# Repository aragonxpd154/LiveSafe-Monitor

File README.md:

# LiveSafe Monitor

Monitoração de sinal de TV e rádio para rodar em Raspberry Pi. Cada Pi fica num abrigo, recebe o sinal do receptor por uma placa de captura HDMI-USB, detecta falhas sozinho e manda trap SNMP. Um servidor LiveSafe central reúne todos os Pis numa tela só e redistribui o vídeo ao vivo de cada local pelo navegador, com um player parecido com o do YouTube.

> **Novo: Placa LiveSafe.** O repositório agora traz também o hardware próprio do LiveSafe — uma placa com
> Raspberry Pi CM4 que recebe **RF ISDB-Tb, HDMI e ASI** direto, sem receptor e sem placa de captura USB, com
> relés e entradas para a remota do abrigo. Esquemático, PCB de 4 camadas e arquivos prontos para a JLCPCB.
> Veja [Placa LiveSafe](#placa-livesafe-hardware).

## O que ele detecta

| Falha | Como | Trap (alarme / normalizado) |
| --- | --- | --- |
| Imagem congelada | menos de 0,1 % dos pixels mudando por 10 s | 2 / 12 |
| Áudio em silêncio | nível abaixo de −60 dBFS por 10 s | 3 / 13 |
| Tela preta | 98 % da tela escura por 5 s | 4 / 14 |
| Sem sinal na entrada | placa ou stream sem entregar dados por 8 s | 5 / 15 |
| Sem comunicação com o Pi (só no central) | Pi não responde por 10 s | 6 / 16 |

Os tempos e limiares são configuráveis por canal. Tela preta tem prioridade sobre congelamento (uma tela preta também está "parada" e não deve gerar dois alarmes). Durante uma queda de sinal os outros detectores ficam suspensos, então não chegam traps falsas de congelamento ou silêncio.

## Como funciona

```
 Abrigo (um Pi em cada)                         Sala de controle

 Receptor ──HDMI──▶ placa HDMI-USB ──USB──┐
                                          ▼
 ┌─────────────────────────────────────────┐   HTTP/TCP    ┌──────────────────────────────┐
 │ Raspberry Pi 4 - LiveSafe de borda      │──────────────▶│ Servidor LiveSafe central    │
 │  • detecta falhas e manda traps         │ estado (SSE)  │  • estado de todos os Pis    │
 │  • gera o stream HLS na RAM             │ vídeo (HLS)   │  • alarme "sem comunicação"  │──▶ navegadores
 └─────────────────────────────────────────┘               │  • repassa o vídeo com cache │    (painel e player)
                                                           └──────────────────────────────┘
```

- **Um ffmpeg por canal.** Decodifica uma única vez e entrega: quadros 160×90 em cinza para a análise, áudio de 16 kHz para os medidores, um JPEG por segundo para a miniatura e o stream ao vivo em HLS (H.264 + AAC).
- **Sem UDP no enlace.** Tudo entre o Pi e o central é HTTP sobre TCP: o estado vai por uma única conexão Server-Sent Events e o vídeo em segmentos HLS de 1 s. Nada de multicast ou fluxo UDP contínuo saindo do abrigo.
- **O enlace só carrega o que está sendo assistido.** O central busca cada segmento do Pi uma vez e entrega para todos que estão assistindo. Dez pessoas olhando Pedra Azul geram um único download até Pedra Azul.
- **Buffer pequeno.** Segmentos de 1 s e player sincronizado a 3 segmentos do ao vivo: atraso típico de 3 a 4 s. A barra do player permite voltar até 30 s.
- **Feito para o Pi.** Codificação H.264 por hardware (`h264_v4l2m2m`) no Pi 4, com troca automática para software se o hardware não estiver disponível. O HLS fica em `/run/livesafe` (RAM) e o log vai para o journald, então o cartão SD quase não é escrito.
- **Se recupera sozinho**, em camadas (detalhes abaixo).
- **Leve.** Só duas dependências npm (`net-snmp` e o `hls.js` do player), servidor HTTP nativo do Node, painel sem CDN que funciona numa rede sem internet.

## Recuperação automática

Um Pi num abrigo não tem ninguém do lado para apertar botão, então cada tipo de falha tem quem cuide dela:

| O que acontece | Quem resolve | Tempo até voltar |
| --- | --- | --- |
| Pi reinicia (falta de energia, reboot) | systemd sobe o LiveSafe no boot; se a placa HDMI-USB demorar a aparecer, a captura tenta de novo sozinha | o tempo do boot + até 30 s |
| ffmpeg cai | LiveSafe religa com espera crescente (2, 4, 8… até 30 s) | 2 s na primeira vez |
| ffmpeg trava sem cair (comum com placa USB) | vigia interno: 8 s sem quadros ou áudio, mata e religa | ~10 s |
| Entrada normal, mas o stream ao vivo parou | vigia interno: playlist parada por 10 s, reinicia a captura e registra a ocorrência | ~15 s |
| LiveSafe cai | systemd religa em 3 s e derruba junto qualquer ffmpeg órfão | 3 s |
| LiveSafe trava sem cair | `livesafe-watchdog.timer`: a cada 30 s testa o `/healthz`; 3 falhas seguidas, reinicia o serviço | até ~1 min |
| Memória dispara | teto de 1,2 GB no systemd; o serviço é reiniciado | 3 s |
| Pi inteiro congela (kernel, calor) | watchdog de hardware do Raspberry Pi: reinicia a placa | 14 s + boot |
| Enlace com o abrigo cai | central alarma "sem comunicação", reconecta sozinho e traz as ocorrências do período fora; o player tenta de novo a cada 3 s | assim que o enlace volta |

Num Raspberry Pi, o instalador pergunta se deve ligar o watchdog de hardware (recomendado; pode pedir um reboot na primeira vez). O que o vigia fez fica em `journalctl -t livesafe-watchdog`.

## Player ao vivo

Clique em **Assistir ao vivo** em qualquer canal. A barra mostra o que já foi carregado (cinza claro) e onde você está (vermelho); o selo **Ao vivo** fica vermelho quando você está na ponta e, se você voltar no tempo, um clique nele traz de volta. **Estatísticas** mostra resolução, taxa, banda medida, buffer à frente, atraso em relação ao ao vivo e quadros perdidos. Atalhos: espaço pausa, `M` silencia, `F` tela cheia, setas voltam ou avançam 5 s.

Canais só de áudio (rádios FM) ganham medidores grandes no lugar da imagem e o botão **Ouvir ao vivo**.

| Pi de borda | Celular |
| :---: | :---: |
|  |  |

## Instalação

Requisitos: Raspberry Pi 4 (2 GB ou mais) com Raspberry Pi OS Bookworm 64 bits, de preferência a versão Lite. O servidor central pode ser outro Pi ou qualquer Debian/Ubuntu.

A instalação tem duas partes: o **instalador** pergunta pelo terminal (SSH) o papel da máquina, o nome do local e a senha do painel, e instala tudo; depois, o **assistente no navegador** configura a placa de captura (Pi) ou os Pis dos abrigos (central).

### 1. Instalar

Escolha um dos três caminhos. Os três usam o mesmo instalador e servem tanto para o Pi de borda quanto para o central.

**Com internet (GitHub):**

```bash
curl -fsSL https://raw.githubusercontent.com/aragonxpd154/LiveSafe-Monitor/main/install.sh | sudo bash
```

**Pelo servidor central**, para Pis que enxergam o central mas não a internet. O assistente do central mostra este comando já com o IP certo:

```bash
curl -fsSL http://<ip-do-central>:8080/instalar.sh | sudo bash
```

**Sem internet (pendrive).** Baixe `livesafe-offline-arm64.tar.gz` na página de [releases](https://github.com/aragonxpd154/LiveSafe-Monitor/releases/latest). O arquivo tem cerca de 250 MB e já traz o ffmpeg, o Node.js e todas as dependências para o Raspberry Pi OS Bookworm 64 bits. No Pi:

```bash
tar -xzf livesafe-offline-arm64.tar.gz
sudo ./livesafe-monitor/install.sh
```

Se o central for instalado a partir do pacote offline, ele guarda esses pacotes e os entrega aos Pis que instalarem pelo segundo caminho. Assim, um Pi sem internet instala tudo só falando com o central.

**Gerar o pacote offline no seu PC.** Não precisa de Pi nem de sudo: qualquer computador Debian/Ubuntu com internet (Zorin OS, por exemplo) monta o pacote para o Raspberry Pi OS Bookworm 64 bits, sem instalar nada no PC:

```bash
sudo apt install dpkg-dev debian-archive-keyring gnupg curl   # só na primeira vez
./scripts/build-offline-bundle.sh --pi                         # gera dist/livesafe-offline-arm64.tar.gz
```

O script baixa os pacotes dos repositórios oficiais do Debian e do Raspberry Pi, conferindo as assinaturas, e leva poucos minutos. Rodando com `sudo` e sem `--pi` num Pi com internet, ele gera o pacote para o sistema daquele Pi. O GitHub Actions também gera os dois pacotes a cada tag `v*` (workflow `release.yml`).

Rodar o instalador de novo atualiza o LiveSafe e mantém a configuração, os canais e as senhas.

<details>
<summary>Instalação automatizada, sem perguntas</summary>

```bash
curl -fsSL …/install.sh | sudo LIVESAFE_NONINTERACTIVE=1 LIVESAFE_ROLE=edge LIVESAFE_SITE="Pedra Azul" LIVESAFE_PASSWORD='…' bash
```

`LIVESAFE_ROLE` é `edge` ou `central`. Sem `LIVESAFE_PASSWORD`, uma senha é gerada e mostrada no fim. `LIVESAFE_HW_WATCHDOG=0` não liga o watchdog de hardware.
</details>

### 2. Configurar no navegador

Ao terminar, o instalador mostra o endereço `http://<ip>:8080/setup`. Entre com o usuário `admin` e a senha que você criou.

- **No Pi de borda**, o assistente procura a placa HDMI-USB, sugere o formato e a resolução, e o botão **Testar entrada** mostra um quadro do receptor e o nível do áudio antes de salvar. Também dá para usar um endereço de rede (UDP do IRD, RTSP, HTTP) ou montar um canal só de rádio.
- **No central**, você cadastra cada Pi pelo IP e pela senha dele; **Testar conexão** confirma o nome do abrigo e os canais.
- As etapas seguintes definem os destinos das traps, os tempos de alarme e a qualidade do vídeo ao vivo. Ao salvar, o LiveSafe reinicia já com a configuração nova.

| Pi de borda: entrada de sinal | Central: Pis dos abrigos |
| :---: | :---: |
|  |  |

O assistente continua disponível em `/setup` para mudanças futuras. Logs ao vivo: `journalctl -u livesafe -f`.

## Configuração manual

O assistente grava `/var/lib/livesafe/config.json`, que também pode ser editado à mão (depois, `sudo systemctl restart livesafe`). Há dois exemplos: [`config.edge.example.json`](config.edge.example.json) (Pi de borda) e [`config.central.example.json`](config.central.example.json) (servidor central). A senha do painel é guardada como hash (`passwordHash`); `password` em texto também é aceito.

### Canal com placa HDMI-USB

As placas baratas com chip MS2109 entregam MJPEG e aparecem como duas entradas: vídeo em `/dev/video0` e áudio no ALSA.

```json
{
  "id": "hdmi",
  "name": "Receptor TV Gazeta (HDMI)",
  "inputArgs": [
    "-f", "v4l2", "-input_format", "mjpeg", "-video_size", "1280x720", "-framerate", "30", "-i", "/dev/video0",
    "-f", "alsa", "-channels", "2", "-sample_rate", "48000", "-i", "hw:CARD=MS2109,DEV=0"
  ],
  "videoStream": "0:v:0",
  "audioStream": "1:a:0"
}
```

Outras entradas que o ffmpeg abre também servem, com `"url"` no lugar de `inputArgs`: `udp://@239.10.10.1:1234` (IRD), `rtsp://…`, `http://…`. Para escolher um serviço dentro de um transport stream com vários programas, use por exemplo `"videoStream": "0:p:57345:v:0"`. Rádio só com áudio: `"video": false`.

### Servidor central

```json
"sites": [
  { "id": "pedra-azul", "name": "Pedra Azul", "url": "http://10.10.8.21:8080", "user": "livesafe", "password": "…" }
]
```

`user` e `password` são o usuário e a senha do painel daquele Pi.

### Ajustes mais usados

| Chave | Padrão | Para que serve |
| --- | --- | --- |
| `freeze.seconds`, `freeze.motionPct` | 10 s, 0,1 % | Tolerância a cenas paradas (cartelas, vinhetas). Veja o "Movimento" no painel para calibrar. |
| `black.seconds`, `black.pct` | 5 s, 98 % | Tela preta. |
| `silence.seconds`, `silence.dbfs` | 10 s, −60 dBFS | Silêncio. Rádio costuma precisar de mais tempo. |
| `signal.stallSeconds` | 8 s | Tempo sem dados até "sem sinal". |
| `stream.bitrate`, `stream.width`, `stream.fps` | 2000k, 1280, 25 | Qualidade do vídeo ao vivo. Reduza se o enlace do abrigo for estreito. |
| `stream.windowSeconds` | 30 | Quanto dá para voltar na barra do player. |
| `stream.encoder` | `auto` | `auto`, `h264_v4l2m2m` (hardware do Pi 4) ou `libx264`. |
| `stream.softwareMaxWidth` | 854 | Largura máxima quando a codificação cai para software, para não saturar a CPU. |
| `central.offlineSeconds` | 10 | Tempo sem resposta até "sem comunicação com o Pi". |
| `snmp.traps.version` | `"1"` | `"1"` (como nas versões anteriores) ou `"2c"`. |
| `snmp.agent.enabled` | `false` | Liga o agente SNMP para o NMS consultar o estado (GET/WALK). |

## SNMP

Toda trap leva os mesmos varbinds, sob o enterprise `1.3.6.1.4.1.53864` usado desde a primeira versão:

| OID | Tipo | Conteúdo |
| --- | --- | --- |
| `.1.1` | Integer | código da tabela acima (1 = LiveSafe iniciado, 9 = trap de teste) |
| `.1.2` | Integer | número do canal |
| `.1.3` | OctetString | nome do canal |
| `.1.4` | OctetString | mensagem em português |
| `.1.5` | OctetString | id do canal |

Em SNMPv1 a trap vai como enterprise `1.3.6.1.4.1.53864.0`, specific = código; em v2c o `snmpTrapOID` é `1.3.6.1.4.1.53864.0.<código>`. O botão **Enviar trap de teste** no painel serve para conferir a chegada no NMS.

Com o agente ligado, a tabela `1.3.6.1.4.1.53864.2.1.1.<coluna>.<canal>` traz índice, id, nome, estado geral (1 normal, 2 observação, 3 alarme, 4 iniciando), estado de sinal, congelamento, tela preta e silêncio (0 desligado, 1 normal, 2 suspeita, 3 alarme), movimento ×100, nível de áudio em dBFS ×10 e reinícios. `1.3.6.1.4.1.53864.3.2.0` é o total de alarmes ativos.

```bash
snmpwalk -v2c -c public <ip-do-pi>:1161 1.3.6.1.4.1.53864
```

## API

| Método e rota | O que faz |
| --- | --- |
| `GET /api/state` | Estado completo (canais, Pis, saúde, últimas ocorrências) |
| `GET /api/stream` | Estado ao vivo por Server-Sent Events |
| `GET /api/events?limit=100` | Histórico de ocorrências |
| `GET /hls/<canal>/index.m3u8` | Stream ao vivo do canal (abre também no VLC) |
| `GET /api/channels/<canal>/snapshot.jpg` | Última miniatura |
| `GET /api/channels/<canal>/live.mjpg` | MJPEG contínuo, para multiviewers |
| `POST /api/channels/<canal>/restart` | Reinicia a captura |
| `POST /api/test-trap` | Envia trap de teste |
| `GET /healthz` | Saúde do serviço, sem autenticação; responde 503 se o laço interno parou (usado pelo vigia) |
| `/sites/<pi>/…` | No central: as mesmas rotas de um Pi, repassadas com cache |

## Testar sem placa de captura

```bash
./scripts/test-signal.sh udp://127.0.0.1:5000
```

Gera um sinal em loop com trechos de imagem normal, congelada, preta e silêncio. Aponte um canal para `udp://127.0.0.1:5000` e acompanhe os alarmes. Parar o script testa o "sem sinal". Testes automáticos: `npm test`.

## Placa LiveSafe (hardware)

Hoje o LiveSafe roda num Raspberry Pi 4 com uma placa de captura HDMI-USB ligada ao receptor. A Placa LiveSafe
junta tudo numa placa só, instalada em cada abrigo, e acrescenta as entradas que faltavam:

| Entrada | Caminho | O que o LiveSafe ganha |
|---|---|---|
| **RF ISDB-Tb (UHF)** | BNC 75 Ω → Si2141 → Si2183-B60 → FX2LP → USB | o sinal do ar, sem IRD; C/N e BER do canal |
| **HDMI** | HDMI → TC358743XBG → CSI-2 (4 vias) + I2S | a saída do IRD/receptor sem placa de captura |
| **ASI** | BNC 75 Ω → GS2961A → FX2LP → USB | o transport stream do encoder ou do multiplexador |

Saídas: Ethernet Gigabit (painel web, HLS, SNMP), 4 relés SPDT e 4 entradas optoacopladas para a remota do
abrigo, RTC com bateria, controle de ventoinha. Alimentação única de **12 V** (9 a 18 V). O software é este
mesmo LiveSafe Monitor; o que muda no lado do software está em [docs/06](docs/06-software-e-drivers.md).

### Situação

| Etapa | Situação |
|---|---|
| Escolha dos chips e arquitetura | ✅ [docs/01](docs/01-arquitetura.md) |
| Pinagens conferidas nos datasheets (Si2183, Si2141, GS2961A) | ✅ `tools/pinagens.py` |
| Esquemático (9 folhas, netlist conferida pelo KiCad) | ✅ [PDF](hardware/esquema-eletrico-completo.pdf) · [docs/02](docs/02-esquematico.md) |
| PCB 4 camadas 160 × 100 mm — **DRC limpo (0 erros, 0 ligações pendentes)** | ✅ [docs/03](docs/03-pcb.md) |
| Arquivos JLCPCB (Gerber, BOM com código LCSC, CPL, STEP) | ✅ [docs/04](docs/04-fabricacao-jlcpcb.md) |
| Protótipo de bancada com módulos prontos | ⏳ [docs/07](docs/07-prototipo-de-bancada.md) |
| Primeira placa fabricada e testada | ⏳ [docs/05](docs/05-montagem-e-testes.md) |

> **Revisão antes de fabricar.** É a revisão 1.0, nunca fabricada. Os pontos em aberto estão em
> [docs/08](docs/08-revisao-e-riscos.md): rede de entrada de RF do Si2141 (datasheet completo sob NDA), pares
> diferenciais roteados automaticamente, disponibilidade do TC358743 e as rotações da montagem JLCPCB.
> Recomenda-se a revisão de um projetista de hardware e um lote pequeno (5 placas) antes da produção.

| Topo | Fundo |
| :---: | :---: |
|  |  |

O [visualizador 3D](docs/3d/visualizador.html) abre o modelo com as camadas reais de cobre, máscara e serigrafia
(com o GitHub Pages ligado no repositório, ele abre direto em
`https://aragonxpd154.github.io/LiveSafe-Monitor/docs/3d/visualizador.html`). O modelo mecânico está em
`hardware/fabricacao/livesafe-placa/livesafe-placa.step`.

### Fabricar

1. Gerber: `hardware/fabricacao/livesafe-placa/livesafe-placa-gerber.zip` — 4 camadas, 1,6 mm, impedância
   controlada **JLC04161H-7628**, ENIG.
2. Montagem: `bom-jlcpcb.csv` + `cpl-jlcpcb.csv` (face de cima), com código LCSC em todas as linhas. Conferir
   as rotações na pré-visualização.
3. `pecas-fora-da-jlcpcb.csv`: conectores de furo (solda manual), TC358743 e indutor de 6,8 µH (*Global
   Sourcing*), CM4 (CM4104032) e bateria CR1220, que entram depois, à mão.

Passo a passo completo em [docs/04](docs/04-fabricacao-jlcpcb.md); primeiros testes em [docs/05](docs/05-montagem-e-testes.md).

### Arquivos da placa

| Pasta | O que tem |
|---|---|
| `hardware/kicad/livesafe-placa/` | projeto KiCad 7 (esquemático hierárquico e PCB) |
| `hardware/kicad/bibliotecas/` | símbolos e footprints próprios (CM4, TC358743 BGA-64 0,65 mm, Si2141 com pads de canto) |
| `hardware/fabricacao/livesafe-placa/` | Gerber, BOM, CPL, STEP, PDFs de conferência, relatório de DRC |
| `hardware/esquema-eletrico-completo.pdf` | o esquema completo |
| `docs/` | arquitetura, esquemático, PCB, fabricação, testes, software, protótipo de bancada, riscos; imagens e 3D |
| `tools/gerador-kicad/` | o gerador: `designs.py` (todas as ligações), `layouts.py` (planta), `pcbgen.py`, `completar.py` (roteador de acabamento), `lcsc.py` (códigos LCSC), `fabricacao.py` |
| `ref/` | pinagens conferidas (JSON) e referências de terceiros |

<details>
<summary>Gerar a placa de novo a partir do código</summary>

```bash
sudo apt install kicad openjdk-21-jre xvfb python3-pip  # KiCad 7 ou mais novo
pip install trimesh cascadio playwright pillow numpy pypdf
cd tools/gerador-kicad
wget https://github.com/freerouting/freerouting/releases/download/v1.9.0/freerouting-1.9.0.jar
/usr/bin/python3 gerar_tudo.py              # esquemático, PCB roteada (Freerouting + completar.py), DRC e JLCPCB
python3 ../diagramas.py                     # diagrama de blocos
python3 ../render3d.py && python3 ../render_imagens3d.py   # modelo 3D e imagens
```

O Freerouting não é determinístico: cada rodada sai diferente e pode precisar de acabamento
([docs/03](docs/03-pcb.md)). A placa versionada é a referência. Para só atualizar valores e códigos das peças
sem mexer no cobre: `sincronizar.py`. Regerar **substitui** os arquivos do KiCad.
</details>

## Estrutura

```
install.sh      instalador com telas no terminal (online, pelo central ou offline)
src/
  index.js      inicialização, laço de 1 s, /healthz e encerramento limpo
  channel.js    um canal: processo ffmpeg, análise, religamento, HLS
  detectors.js  análise de quadro, níveis de áudio e histerese
  encoder.js    escolha do encoder H.264 (hardware do Pi ou software)
  remote.js     servidor central: conexão com os Pis e cache do proxy
  setup.js      assistente: testar entrada, testar Pi, salvar e reiniciar
  devices.js    descoberta de placas V4L2 e ALSA
  installer.js  /instalar.sh e o pacote servidos pelo central
  auth.js       senha do painel (hash scrypt, bloqueio após erros)
  snmp.js       traps e agente SNMP
  web.js        servidor HTTP, SSE, HLS e proxy
  events.js     histórico de ocorrências
  system.js     temperatura, CPU e memória do host
public/         painel, player e assistente (sem dependências externas)
deploy/         instalação sem perguntas, serviço systemd e vigia (watchdog)
scripts/        descoberta de placas, sinal de teste e geração dos pacotes
legacy/         versões 1 a 4, só para consulta

hardware/       Placa LiveSafe: projeto KiCad, esquema em PDF e arquivos de fabricação (JLCPCB)
docs/           documentação da placa (01 a 08), imagens e visualizador 3D
tools/          gerador da placa por código (KiCad + Freerouting) e scripts das imagens
ref/            pinagens conferidas nos datasheets e referências de terceiros
```

## Histórico

A versão 5 reescreve o projeto. As versões anteriores dependiam de uma aba do navegador aberta (v1/v2) ou do Windows com DirectShow (v3), e o painel vinha de outro projeto, com bibliotecas carregadas de CDNs que já saíram do ar. O código antigo está em [`legacy/`](legacy/), sem os executáveis do ffmpeg para Windows que ocupavam cerca de 500 MB do repositório.

Em novembro de 2026 entrou a **Placa LiveSafe** (revisão 1.0 do hardware), descrita acima e no
[CHANGELOG](CHANGELOG.md).

## Autor

**Marcos Silva dos Santos** (MarcosObel) — [github.com/aragonxpd154](https://github.com/aragonxpd154)

## Licença

- **Software** (`src/`, `public/`, `deploy/`, `scripts/`, `install.sh` e o resto do LiveSafe Monitor): **MIT**.
  Veja [LICENSE](LICENSE).
- **Placa LiveSafe** (`hardware/`, `docs/`, `tools/`, `ref/`): **CERN-OHL-S-2.0**. Veja
  [hardware/LICENSE](hardware/LICENSE). Partes de terceiros mantêm a licença original: circuito de referência
  do TC358743 e footprint do DF40 (Antmicro, Apache-2.0), footprint do CM4 (Raspberry Pi Ltd., projeto KiCad da
  placa CM4IO, CC BY 4.0), SDK do Si2183/Si2141 (Skyworks, Apache-2.0).

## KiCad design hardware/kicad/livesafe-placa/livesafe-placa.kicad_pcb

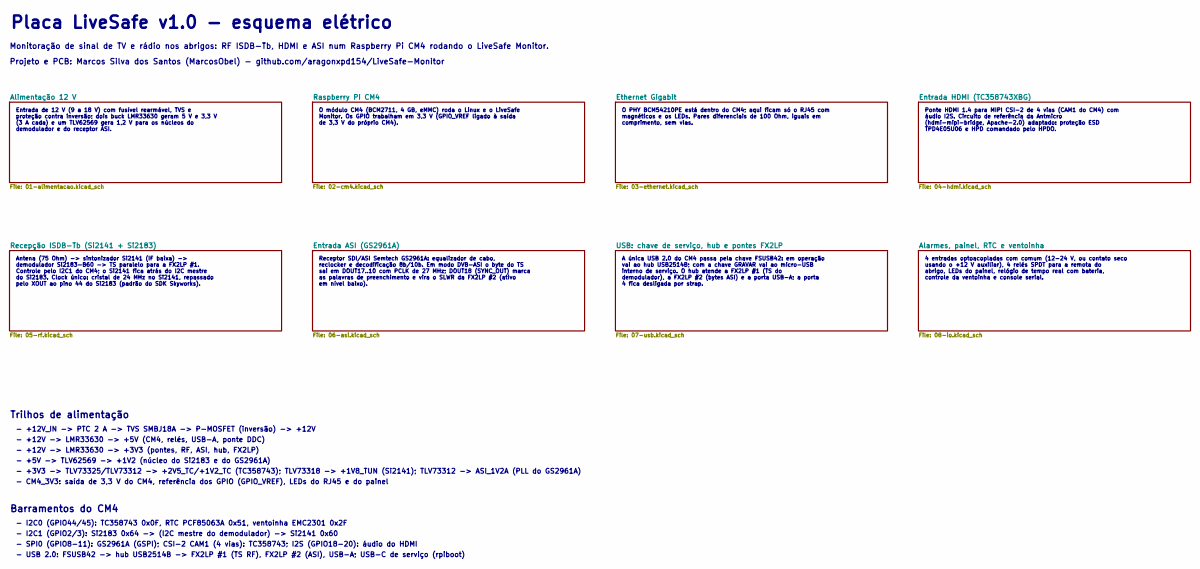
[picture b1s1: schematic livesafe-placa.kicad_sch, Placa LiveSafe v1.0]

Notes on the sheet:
Placa LiveSafe v1.0 - esquema elétrico
Monitoração de sinal de TV e rádio nos abrigos: RF ISDB-Tb, HDMI e ASI num Raspberry Pi CM4 rodando o LiveSafe Monitor.
Projeto e PCB: Marcos Silva dos Santos (MarcosObel) - github.com/aragonxpd154/LiveSafe-Monitor
Entrada de 12 V (9 a 18 V) com fusível rearmável, TVS e proteção contra inversão; dois buck LMR33630 geram 5 V e 3,3 V (3 A cada) e um TLV62569 gera 1,2 V para os núcleos do demodulador e do receptor ASI.
O módulo CM4 (BCM2711, 4 GB, eMMC) roda o Linux e o LiveSafe Monitor. Os GPIO trabalham em 3,3 V (GPIO_VREF ligado à saída de 3,3 V do próprio CM4).
O PHY BCM54210PE está dentro do CM4; aqui ficam só o RJ45 com magnéticos e os LEDs. Pares diferenciais de 100 Ohm, iguais em comprimento, sem vias.
Ponte HDMI 1.4 para MIPI CSI-2 de 4 vias (CAM1 do CM4) com áudio I2S. Circuito de referência da Antmicro (hdmi-mipi-bridge, Apache-2.0) adaptado: proteção ESD TPD4E05U06 e HPD comandado pelo HPDO.
Antena (75 Ohm) -> sintonizador Si2141 (IF baixa) -> demodulador Si2183-B60 -> TS paralelo para a FX2LP #1. Controle pelo I2C1 do CM4; o Si2141 fica atrás do I2C mestre do Si2183. Clock único: cristal de 24 MHz no Si2141, repassado pelo XOUT ao pino 44 do Si2183 (padrão do SDK Skyworks).
Receptor SDI/ASI Semtech GS2961A: equalizador de cabo, reclocker e decodificação 8b/10b. Em modo DVB-ASI o byte do TS sai em DOUT17..10 com PCLK de 27 MHz; DOUT18 (SYNC_OUT) marca as palavras de preenchimento e vira o SLWR da FX2LP #2 (ativo em nível baixo).
A única USB 2.0 do CM4 passa pela chave FSUSB42: em operação vai ao hub USB2514B; com a chave GRAVAR vai ao micro-USB interno de serviço. O hub atende a FX2LP #1 (TS do demodulador), a FX2LP #2 (bytes ASI) e a porta USB-A; a porta 4 fica desligada por strap.
4 entradas optoacopladas com comum (12-24 V, ou contato seco usando o +12 V auxiliar), 4 relés SPDT para a remota do abrigo, LEDs do painel, relógio de tempo real com bateria, controle da ventoinha e console serial.
Trilhos de alimentação
- +12V_IN -> PTC 2 A -> TVS SMBJ18A -> P-MOSFET (inversão) -> +12V
- +12V -> LMR33630 -> +5V (CM4, relés, USB-A, ponte DDC)
- +12V -> LMR33630 -> +3V3 (pontes, RF, ASI, hub, FX2LP)
- +5V -> TLV62569 -> +1V2 (núcleo do Si2183 e do GS2961A)
- +3V3 -> TLV73325/TLV73312 -> +2V5_TC/+1V2_TC (TC358743); TLV73318 -> +1V8_TUN (Si2141); TLV73312 -> ASI_1V2A (PLL do GS2961A)
- CM4_3V3: saída de 3,3 V do CM4, referência dos GPIO (GPIO_VREF), LEDs do RJ45 e do painel
Barramentos do CM4
- I2C0 (GPIO44/45): TC358743 0x0F, RTC PCF85063A 0x51, ventoinha EMC2301 0x2F
- I2C1 (GPIO2/3): Si2183 0x64 -> (I2C mestre do demodulador) -> Si2141 0x60
- SPI0 (GPIO8-11): GS2961A (GSPI); CSI-2 CAM1 (4 vias): TC358743; I2S (GPIO18-20): áudio do HDMI
- USB 2.0: FSUSB42 -> hub USB2514B -> FX2LP #1 (TS RF), FX2LP #2 (ASI), USB-A; USB-C de serviço (rpiboot)

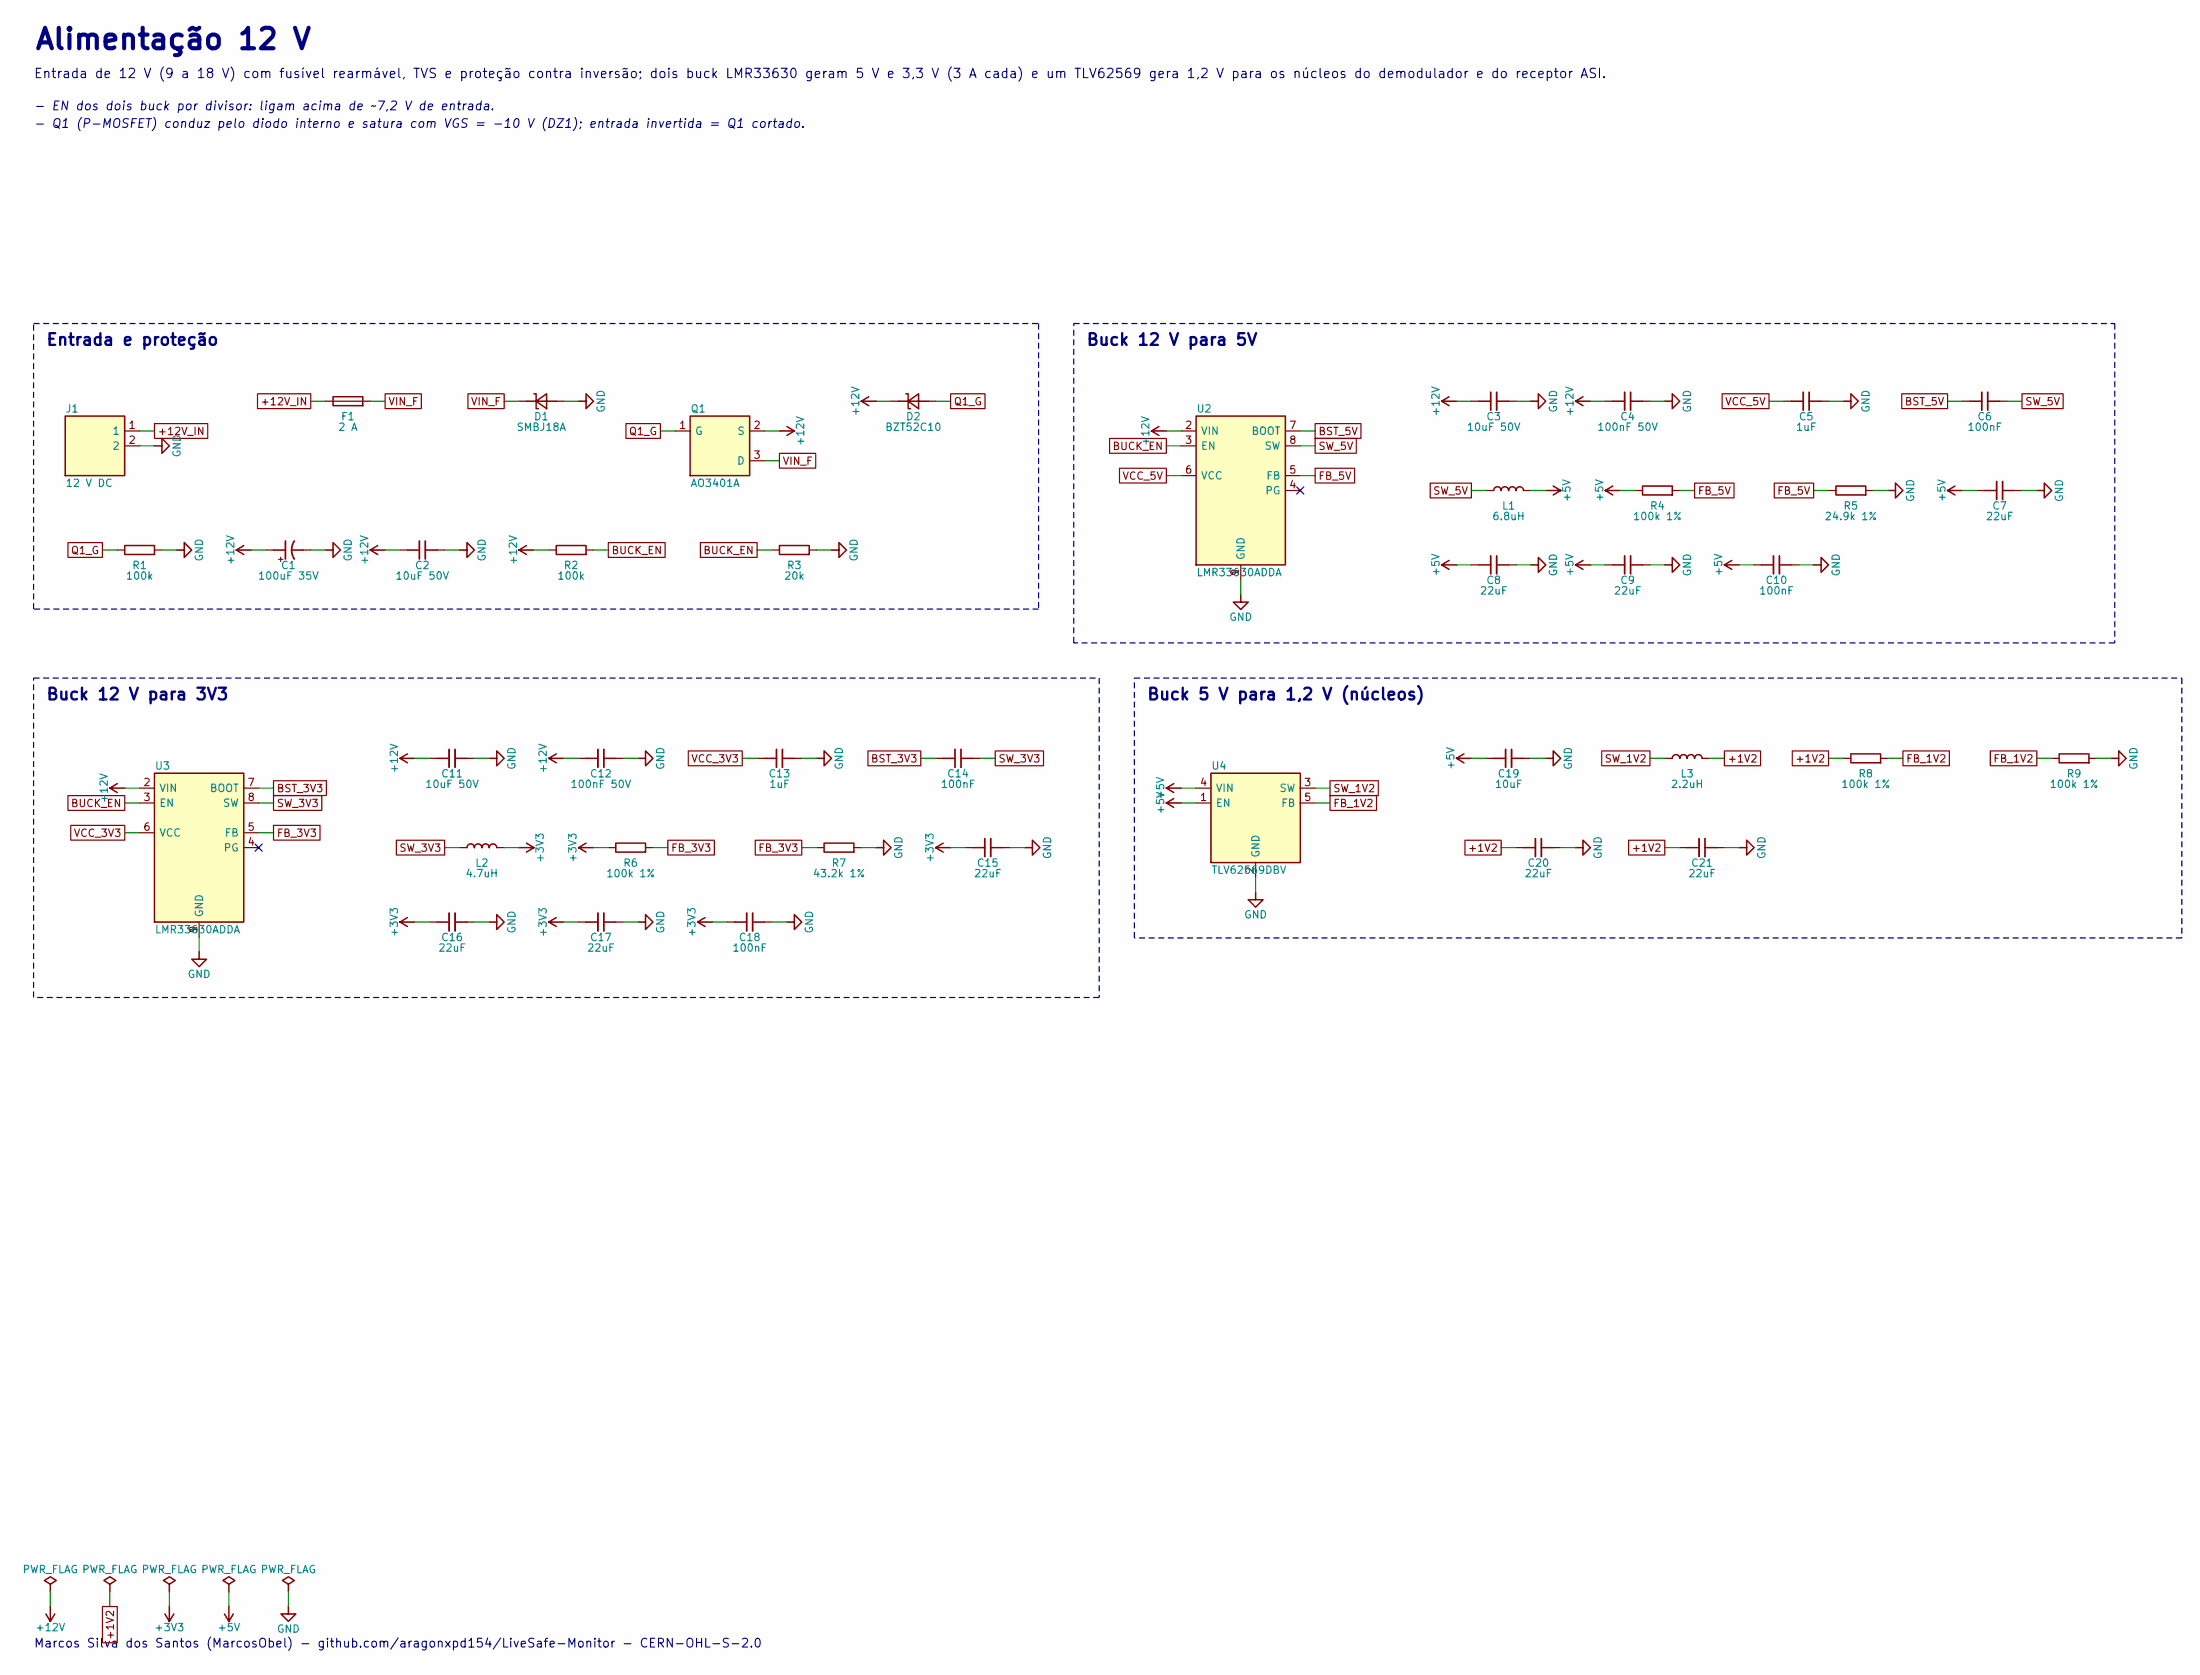
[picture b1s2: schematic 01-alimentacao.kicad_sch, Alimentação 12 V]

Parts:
C1: 100uF 35V; CP_Elec_8x10; MPN EEE-FK1V101P; LCSC C128462
C2, C3, C11: 10uF 50V; C_1210_3225Metric; MPN GRM32ER71H106KA12L; LCSC C77102
C4, C12: 100nF 50V; C_0603_1608Metric; MPN CL10B104KB8NNNC; LCSC C1591
C5, C13: 1uF; C_0402_1005Metric; MPN CL05A105KA5NQNC; LCSC C52923
C6, C10, C14, C18: 100nF; C_0402_1005Metric; MPN CL05B104KO5NNNC; LCSC C1525
C7, C8, C9, C15, C16, C17, C20, C21: 22uF; C_0805_2012Metric; MPN CL21A226MAQNNNE; LCSC C45783
C19: 10uF; C_0603_1608Metric; MPN CL10A106KP8NNNC; LCSC C19702
D1: SMBJ18A; D_SMB; MPN SMBJ18A; LCSC C353379
D2: BZT52C10; D_SOD-123; MPN BZT52C10-7-F; LCSC C155227
F1: 2 A; Fuse_1812_4532Metric; MPN SMD1812P200TF/24; LCSC C434887
J1: 12 V DC; PhoenixContact_MSTBA_2,5_2-G-5,08_1x02_P5.08mm_Horizontal; MPN MSTBA 2,5/2-G-5,08
L1: 6.8uH; L_Bourns_SRP7028A_7.3x6.6mm; MPN SRP7028A-6R8M
L2: 4.7uH; L_Bourns_SRP7028A_7.3x6.6mm; MPN SRP7028A-4R7M; LCSC C840529
L3: 2.2uH; L_1210_3225Metric; MPN LQH32PN2R2NN0L; LCSC C86074
Q1: AO3401A; SOT-23; MPN AO3401A; LCSC C15127
R1, R2: 100k; R_0402_1005Metric; MPN 0402WGF1003TCE; LCSC C25741
R3: 20k; R_0402_1005Metric; MPN 0402WGF2002TCE; LCSC C25765
R4, R6, R8, R9: 100k 1%; R_0402_1005Metric; MPN 0402WGF1003TCE; LCSC C25741
R5: 24.9k 1%; R_0402_1005Metric; MPN 0402WGF2492TCE; LCSC C25874
R7: 43.2k 1%; R_0402_1005Metric; MPN 0402WGF4322TCE; LCSC C25894
U2, U3: LMR33630ADDA; Texas_HSOP-8-1EP_3.9x4.9mm_P1.27mm_ThermalVias; MPN LMR33630ADDAR; LCSC C841384
U4: TLV62569DBV; SOT-23-5; MPN TLV62569DBVR; LCSC C141836

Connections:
+1V2: C20.1, C21.1, L3.2, R8.1; also elsewhere on the board
+3V3: C15.1, C16.1, C17.1, C18.1, L2.2, R6.1; also elsewhere on the board
+5V: C7.1, C8.1, C9.1, C10.1, C19.1, L1.2, R4.1, U4.1 (EN), U4.4 (VIN); also elsewhere on the board
+12V: C1.1, C2.1, C3.1, C4.1, C11.1, C12.1, D2.1 (K), Q1.2 (S), R2.1, U2.2 (VIN), U3.2 (VIN); also elsewhere on the board
+12V_IN: F1.1, J1.1
BST_3V3: C14.1, U3.7 (BOOT)
BST_5V: C6.1, U2.7 (BOOT)
BUCK_EN: R2.2, R3.1, U2.3 (EN), U3.3 (EN)
FB_1V2: R8.2, R9.1, U4.5 (FB)
FB_3V3: R6.2, R7.1, U3.5 (FB)
FB_5V: R4.2, R5.1, U2.5 (FB)
GND: C1.2, C2.2, C3.2, C4.2, C5.2, C7.2, C8.2, C9.2, C10.2, C11.2, C12.2, C13.2, C15.2, C16.2, C17.2, C18.2, C19.2, C20.2, C21.2, D1.2 (A), J1.2, R1.2, R3.2, R5.2, R7.2, R9.2, U2.1 (GND), U2.9 (GND), U3.1 (GND), U3.9 (GND), U4.2 (GND); also elsewhere on the board
Q1_G: D2.2 (A), Q1.1 (G), R1.1
SW_1V2: L3.1, U4.3 (SW)
SW_3V3: C14.2, L2.1, U3.8 (SW)
SW_5V: C6.2, L1.1, U2.8 (SW)
VCC_3V3: C13.1, U3.6 (VCC)
VCC_5V: C5.1, U2.6 (VCC)
VIN_F: D1.1 (K), F1.2, Q1.3 (D)

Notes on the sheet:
Entrada e proteção
Buck 12 V para 5V
Buck 12 V para 3V3
Buck 5 V para 1,2 V (núcleos)
Alimentação 12 V
Entrada de 12 V (9 a 18 V) com fusível rearmável, TVS e proteção contra inversão; dois buck LMR33630 geram 5 V e 3,3 V (3 A cada) e um TLV62569 gera 1,2 V para os núcleos do demodulador e do receptor ASI.
- EN dos dois buck por divisor: ligam acima de ~7,2 V de entrada.
- Q1 (P-MOSFET) conduz pelo diodo interno e satura com VGS = -10 V (DZ1); entrada invertida = Q1 cortado.
Marcos Silva dos Santos (MarcosObel) - github.com/aragonxpd154/LiveSafe-Monitor - CERN-OHL-S-2.0

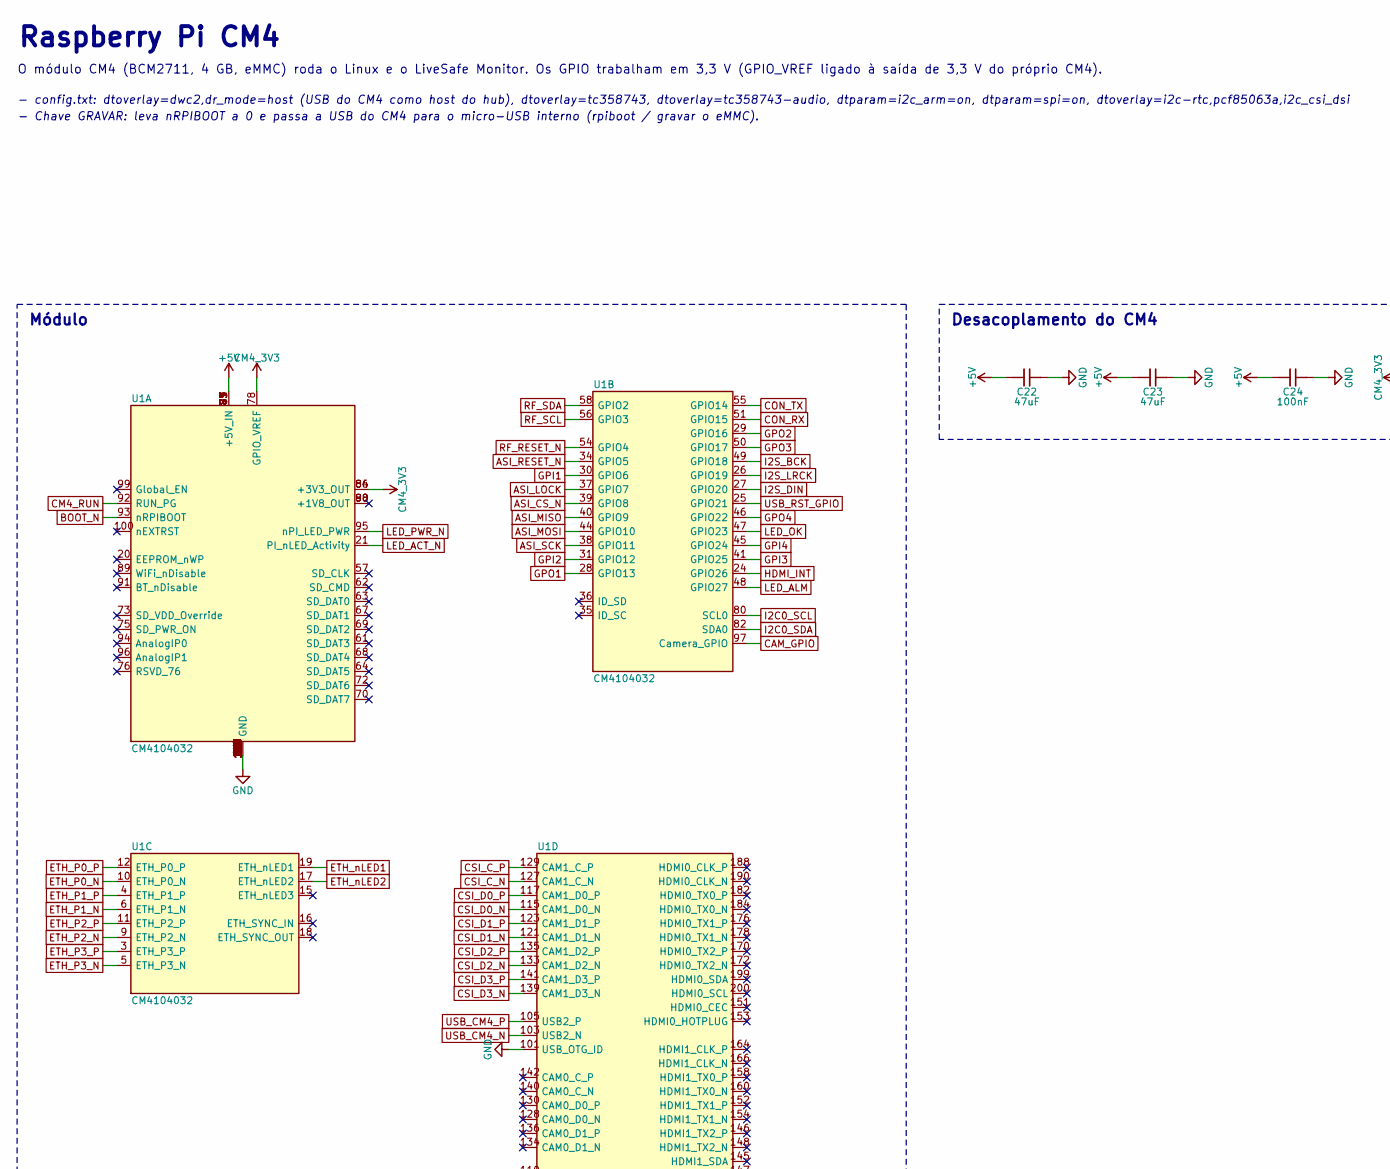
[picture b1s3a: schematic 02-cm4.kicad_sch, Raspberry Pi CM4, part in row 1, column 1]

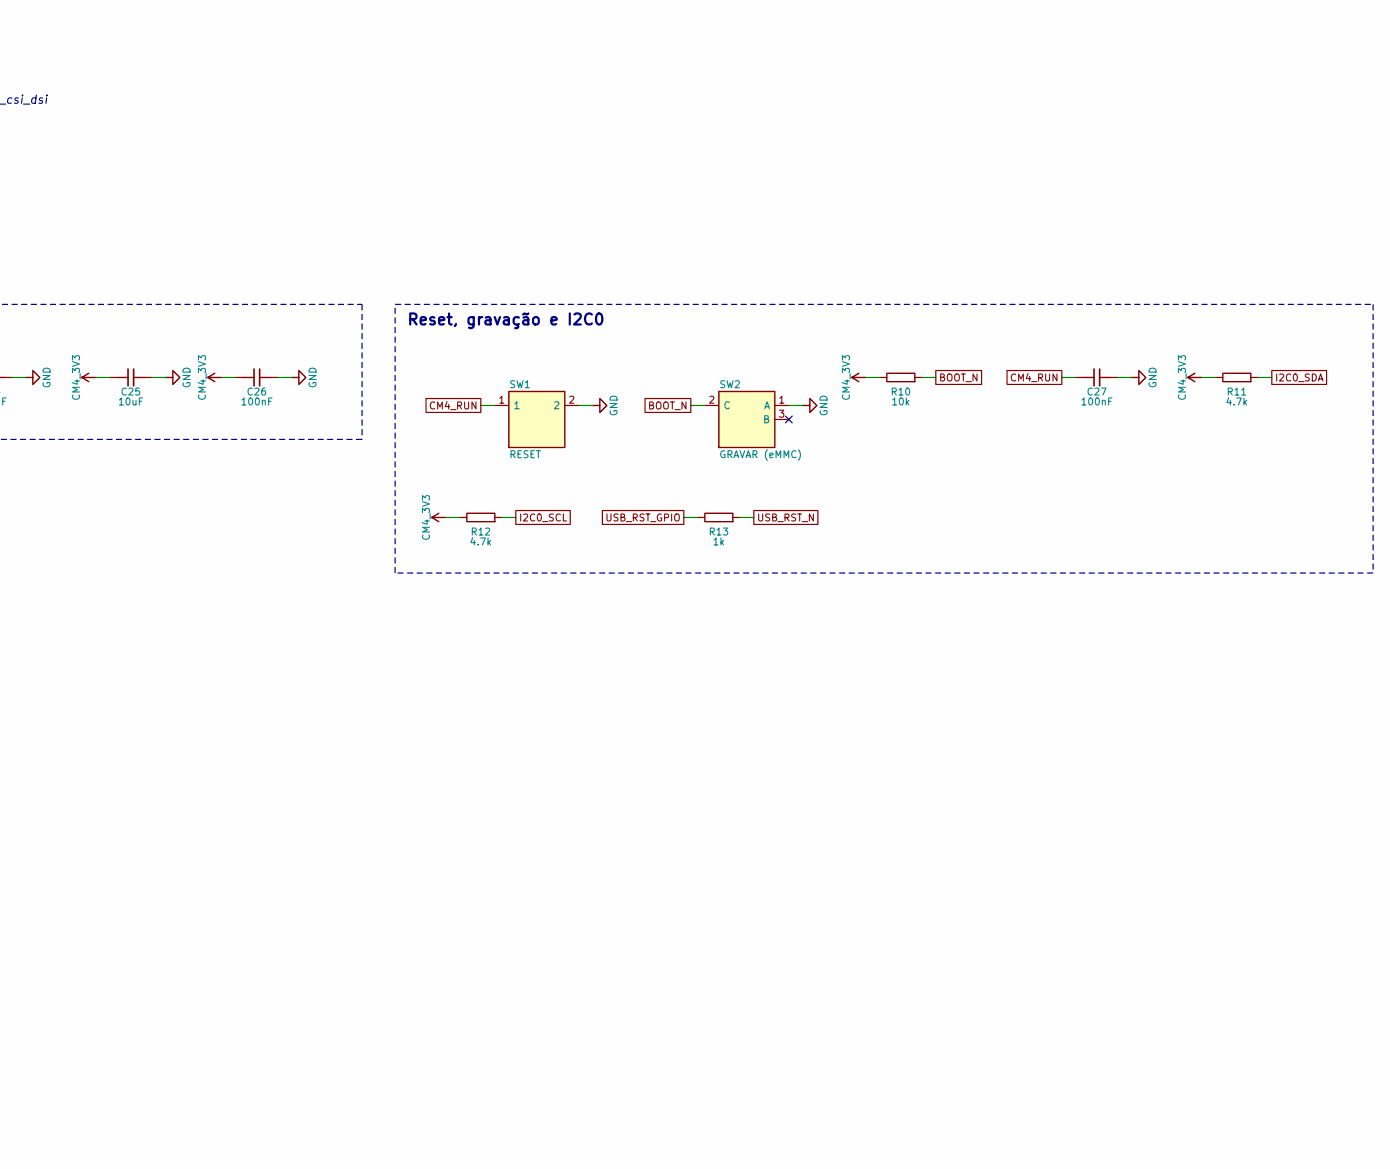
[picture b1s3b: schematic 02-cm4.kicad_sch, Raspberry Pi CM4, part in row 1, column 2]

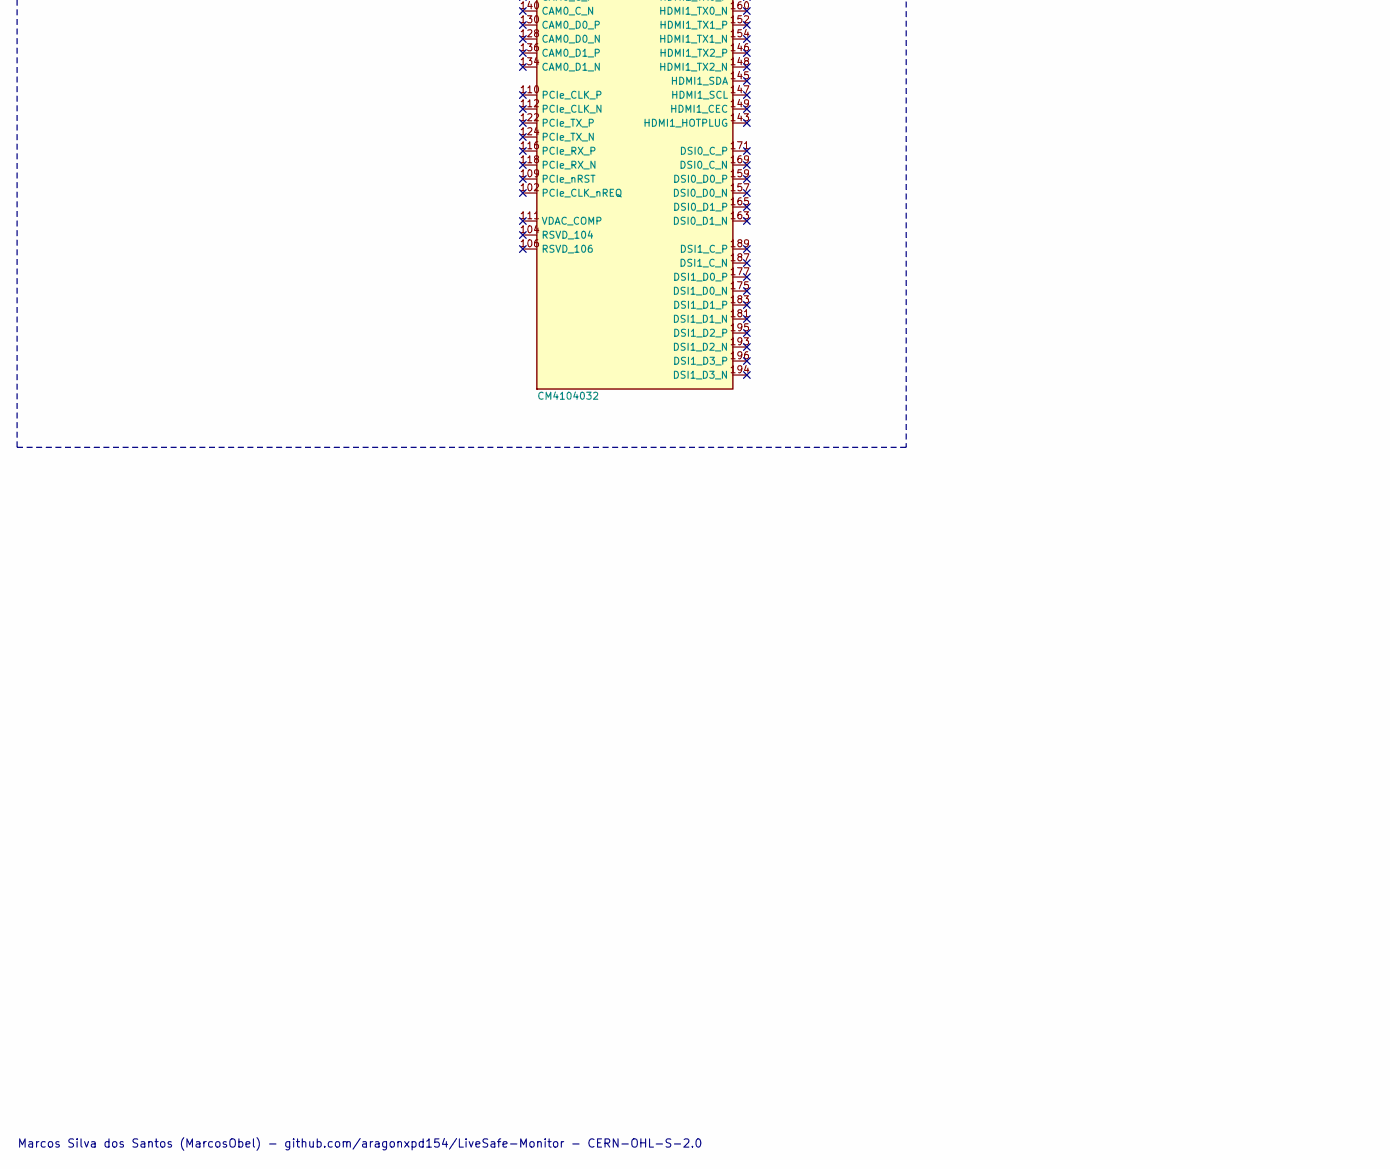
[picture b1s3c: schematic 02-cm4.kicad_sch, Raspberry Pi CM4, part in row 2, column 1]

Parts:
C22, C23: 47uF; C_1206_3216Metric; MPN CL31A476MPHNNNE; LCSC C96123
C24, C26, C27: 100nF; C_0402_1005Metric; MPN CL05B104KO5NNNC; LCSC C1525
C25: 10uF; C_0603_1608Metric; MPN CL10A106KP8NNNC; LCSC C19702
R10: 10k; R_0402_1005Metric; MPN 0402WGF1002TCE; LCSC C25744
R11, R12: 4.7k; R_0402_1005Metric; MPN 0402WGF4701TCE; LCSC C25900
R13: 1k; R_0402_1005Metric; MPN 0402WGF1001TCE; LCSC C11702
SW1: RESET; SW_SPST_TL3342; MPN TL3342F160QG; LCSC C2886898
SW2: GRAVAR (eMMC); SW_SPDT_PCM12; MPN PCM12SMTR; LCSC C221841
U1: CM4104032; Raspberry_Pi_CM4_DF40; MPN CM4104032

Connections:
+5V: C22.1, C23.1, C24.1, U1.77 (+5V_IN), U1.79 (+5V_IN), U1.81 (+5V_IN), U1.83 (+5V_IN), U1.85 (+5V_IN), U1.87 (+5V_IN); also elsewhere on the board
ASI_CS_N: U1.39 (GPIO8); also elsewhere on the board
ASI_LOCK: U1.37 (GPIO7); also elsewhere on the board
ASI_MISO: U1.40 (GPIO9); also elsewhere on the board
ASI_MOSI: U1.44 (GPIO10); also elsewhere on the board
ASI_RESET_N: U1.34 (GPIO5); also elsewhere on the board
ASI_SCK: U1.38 (GPIO11); also elsewhere on the board
BOOT_N: R10.2, SW2.2 (C), U1.93 (nRPIBOOT); also elsewhere on the board
CAM_GPIO: U1.97 (Camera_GPIO); also elsewhere on the board
CM4_3V3: C25.1, C26.1, R10.1, R11.1, R12.1, U1.78 (GPIO_VREF), U1.84 (+3V3_OUT), U1.86 (+3V3_OUT); also elsewhere on the board
CM4_RUN: C27.1, SW1.1, U1.92 (RUN_PG)
CON_RX: U1.51 (GPIO15); also elsewhere on the board
CON_TX: U1.55 (GPIO14); also elsewhere on the board
CSI_C_N: U1.127 (CAM1_C_N); also elsewhere on the board
CSI_C_P: U1.129 (CAM1_C_P); also elsewhere on the board
CSI_D0_N: U1.115 (CAM1_D0_N); also elsewhere on the board
CSI_D0_P: U1.117 (CAM1_D0_P); also elsewhere on the board
CSI_D1_N: U1.121 (CAM1_D1_N); also elsewhere on the board
CSI_D1_P: U1.123 (CAM1_D1_P); also elsewhere on the board
CSI_D2_N: U1.133 (CAM1_D2_N); also elsewhere on the board
CSI_D2_P: U1.135 (CAM1_D2_P); also elsewhere on the board
CSI_D3_N: U1.139 (CAM1_D3_N); also elsewhere on the board
CSI_D3_P: U1.141 (CAM1_D3_P); also elsewhere on the board
ETH_P0_N: U1.10 (ETH_P0_N); also elsewhere on the board
ETH_P0_P: U1.12 (ETH_P0_P); also elsewhere on the board
ETH_P1_N: U1.6 (ETH_P1_N); also elsewhere on the board
ETH_P1_P: U1.4 (ETH_P1_P); also elsewhere on the board
ETH_P2_N: U1.9 (ETH_P2_N); also elsewhere on the board
ETH_P2_P: U1.11 (ETH_P2_P); also elsewhere on the board
ETH_P3_N: U1.5 (ETH_P3_N); also elsewhere on the board
ETH_P3_P: U1.3 (ETH_P3_P); also elsewhere on the board
ETH_nLED1: U1.19 (ETH_nLED1); also elsewhere on the board
ETH_nLED2: U1.17 (ETH_nLED2); also elsewhere on the board
GND: C22.2, C23.2, C24.2, C25.2, C26.2, C27.2, SW1.2, SW2.1 (A), U1.1 (GND), U1.2 (GND), U1.7 (GND), U1.8 (GND), U1.13 (GND), U1.14 (GND), U1.22 (GND), U1.23 (GND), U1.32 (GND), U1.33 (GND), U1.42 (GND), U1.43 (GND), U1.52 (GND), U1.53 (GND), U1.59 (GND), U1.60 (GND), U1.65 (GND), U1.66 (GND), U1.71 (GND), U1.74 (GND), U1.98 (GND), U1.101 (USB_OTG_ID), U1.107 (GND), U1.108 (GND), U1.113 (GND), U1.114 (GND), U1.119 (GND), U1.120 (GND), U1.125 (GND), U1.126 (GND), U1.131 (GND), U1.132 (GND), U1.137 (GND), U1.138 (GND), U1.144 (GND), U1.150 (GND), U1.155 (GND), U1.156 (GND), U1.161 (GND), U1.162 (GND), U1.167 (GND), U1.168 (GND), U1.173 (GND), U1.174 (GND), U1.179 (GND), U1.180 (GND), U1.185 (GND), U1.186 (GND), U1.191 (GND), U1.192 (GND), U1.197 (GND), U1.198 (GND); also elsewhere on the board
GPI1: U1.30 (GPIO6); also elsewhere on the board
GPI2: U1.31 (GPIO12); also elsewhere on the board
GPI3: U1.41 (GPIO25); also elsewhere on the board
GPI4: U1.45 (GPIO24); also elsewhere on the board
GPO1: U1.28 (GPIO13); also elsewhere on the board
GPO2: U1.29 (GPIO16); also elsewhere on the board
GPO3: U1.50 (GPIO17); also elsewhere on the board
GPO4: U1.46 (GPIO22); also elsewhere on the board
HDMI_INT: U1.24 (GPIO26); also elsewhere on the board
I2C0_SCL: R12.2, U1.80 (SCL0); also elsewhere on the board
I2C0_SDA: R11.2, U1.82 (SDA0); also elsewhere on the board
I2S_BCK: U1.49 (GPIO18); also elsewhere on the board
I2S_DIN: U1.27 (GPIO20); also elsewhere on the board
I2S_LRCK: U1.26 (GPIO19); also elsewhere on the board
LED_ACT_N: U1.21 (PI_nLED_Activity); also elsewhere on the board
LED_ALM: U1.48 (GPIO27); also elsewhere on the board
LED_OK: U1.47 (GPIO23); also elsewhere on the board
LED_PWR_N: U1.95 (nPI_LED_PWR); also elsewhere on the board
RF_RESET_N: U1.54 (GPIO4); also elsewhere on the board
RF_SCL: U1.56 (GPIO3); also elsewhere on the board
RF_SDA: U1.58 (GPIO2); also elsewhere on the board
USB_CM4_N: U1.103 (USB2_N); also elsewhere on the board
USB_CM4_P: U1.105 (USB2_P); also elsewhere on the board
USB_RST_GPIO: R13.1, U1.25 (GPIO21)
USB_RST_N: R13.2; also elsewhere on the board

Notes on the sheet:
Módulo
Desacoplamento do CM4
Reset, gravação e I2C0
Raspberry Pi CM4
O módulo CM4 (BCM2711, 4 GB, eMMC) roda o Linux e o LiveSafe Monitor. Os GPIO trabalham em 3,3 V (GPIO_VREF ligado à saída de 3,3 V do próprio CM4).
- config.txt: dtoverlay=dwc2,dr_mode=host (USB do CM4 como host do hub), dtoverlay=tc358743, dtoverlay=tc358743-audio, dtparam=i2c_arm=on, dtparam=spi=on, dtoverlay=i2c-rtc,pcf85063a,i2c_csi_dsi
- Chave GRAVAR: leva nRPIBOOT a 0 e passa a USB do CM4 para o micro-USB interno (rpiboot / gravar o eMMC).
Marcos Silva dos Santos (MarcosObel) - github.com/aragonxpd154/LiveSafe-Monitor - CERN-OHL-S-2.0

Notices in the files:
hardware/kicad/livesafe-placa/01-alimentacao.kicad_sch:
Licença CERN-OHL-S-2.0 - gerado por tools/gerador-kicad
hardware/kicad/livesafe-placa/livesafe-placa.kicad_pcb:
Marcos Silva dos Santos (MarcosObel) - CERN-OHL-S-2.0
